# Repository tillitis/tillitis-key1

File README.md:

# Tillitis TKey

Read about current work in progress
[here](#current-work-in-progress-in-this-repository).

 *The TK1 PCB, also known as
TKey.*

## Introduction

The Tillitis TKey is an open source, open hardware FPGA-based USB
security token which can run generic applications while still
guaranteeing the security of its cryptographic assets.

The key behind guaranteeing key security even as a general computer is
the
[DICE-like](https://trustedcomputinggroup.org/work-groups/dice-architectures/)
measured boot or, when chaining apps, the combination of measured boot
and verified boot. You can read more about this in the introduction in
the [TKey Developer Handbook](https://dev.tillitis.se/castor/intro/).

[TKey Threat Model](doc/threat_model/threat_model.md).

With the right application, the TKey can be used for:

- authentication,
- cryptographic signing,
- encryption,
- root of trust,
- and more: it's a general computer!

If you want to know more about Tillitis and the TKey, visit:

- Main web: <https://tillitis.se/>
- Shop: <https://shop.tillitis.se/>
- Developer Handbook: <https://dev.tillitis.se/>
- Officially supported apps: <https://tillitis.se/download/>
- Other known apps: <https://dev.tillitis.se/projects/>

All of the TKey software, firmware, FPGA Verilog code, schematics and
PCB design files are open source, just like all trustworthy security
software and hardware should be.

## Licensing

Unless otherwise noted, the project sources are copyright Tillitis AB,
but you can redistribute it and/or modify it under the terms of the
BSD-2-Clause license.

Until Oct 29, 2025, the license was GPL-2.0 Only.

Each imported project is typically kept in its own directory with its
own LICENSE file.

### SPDX

The project uses single-line references to Unique License Identifiers
as defined by the Linux Foundation's [SPDX project](https://spdx.org/).
The line in each individual source file identifies the license
applicable to that file.

The current set of valid, predefined SPDX identifiers can be found on
the SPDX License List at:

https://spdx.org/licenses/

We attempt to follow the [REUSE
specification](https://reuse.software/).

### Notable imported projects

- ch552 firmware: `hw/usb_interface/ch552_fw/`

  Originally by WCH under MIT. Much changed by Tillitis.

- picorv32: `hw/application_fpga/core/picorv32`

  From https://github.com/YosysHQ/picorv32

  ISC.

- PicoRV32 custom ops: `hw/application_fpga/fw/tk1/picorv32/`

  CC-1.

- tkey-libs: `hw/application_fpga/tkey-libs/`

  BSD2. From https://github.com/tillitis/tkey-libs

## Repositories

This repository contains the FPGA design, the source of the
firmware/bootloader, and the source of the USB controller firmware.

Specific documentation regarding implementation is kept close to the
code/design in README files, typically in the same directory.

Note that development is ongoing. To avoid unexpected changes of
derived key material, please use a tagged release. Read the [Release
Notes](doc/release_notes.md) to keep up to date with changes and new
releases.

The TKey PCB [KiCad](https://www.kicad.org/) design files are kept in
a separate repository:

<https://github.com/tillitis/tk1-pcba>

The TP1 (TKey programmer 1) PCB design files and the firmware sources
are kept in:

<https://github.com/tillitis/tp1>

Note that the TP1 is only used for provisioning the FPGA bitstream
into flash or the FPGA configuration memory. It's not necessary if you
just want to develop apps for the TKey.

We use the tkey-libs libraries used for device app development in the
firmware, too:

https://github.com/tillitis/tkey-libs

but keep our own copy of it in the repo. See below.

## Building & flashing

These instructions assume you're using a Linux distribution. Most of
them also assume you're using our OCI image
[tkey-builder](https://ghcr.io/tillitis/tkey-builder). If you want to
run native tools, look in `contrib/Dockerfile` and
`contrib/buildtools.sh` for the tools and versions to use.

### FPGA

You need a [TKey
Unlocked](https://shop.tillitis.se/products/tkey-not-provisioned), a
[the TP1 TKey Programmer
board](https://shop.tillitis.se/products/tkey-dev-kit), and probably a
[Blinkinlabs CH55x Reset
Controller](https://shop-nl.blinkinlabs.com/products/ch55x-reset-controller)
to use this on real hardware.

Building is probably easiest using make and Podman.

To build everything and then flash the resulting bitstream with the
defaultapp in app slot 0 and the partition table copies in one go,
place the TKey Unlocked in the TP1, then do:

```
cd contrib
make flash
```

This uses the make target `prog_flash` in
`hw/application_fpga/Makefile` behind the scenes, but mounts your TP1
device into the container.

If you want to change the default app the TKey uses, change
`FLASH_APP_0` in the `hw/application_fpga/Makefile`.

To see all container targets:

```
cd contrib
make
```

See the [Tillitis Developer Handbook](https://dev.tillitis.se) for
more.

### USB Controller

The TKey uses a WCH CH552 chip as a USB controller. It has its own
firmware.

Build:

```
cd contrib
make run
cd hw/usb_interface/ch552_fw
make
```

To flash the controller with new firmware you need hardware like the
[Blinkinlabs CH55x Reset
Controller](https://shop-nl.blinkinlabs.com/products/ch55x-reset-controller)
and a USB-A to USB-C converter.

[Reset Controller source](https://github.com/Blinkinlabs/ch55x_programmer).

You also need [chprog](https://github.com/ole00/chprog).

The bootloader identifies itself as USB VID 4348, PID 55e0. To be able
to access it and run `chprog` without root you need to allow your user
to access it. Place `contrib/99-tillitis.rules` in `/etc/udev/rules.d`
and run `udevadm control --reload`. Now you can add your user to the
`dialout` group and access it.

1. Connect the Reset Controller to your computer through "DUT\_IN"/"PC".
2. Connect the TKey to "DUT\_OUT"/"DUT".
3. Press the "Bootloader" button.
4. Run `make flash_patched` in `hw/usb_interface/ch552_fw` outside of
   a container.

## Updating and working with tkey-libs

A copy of [tkey-libs](https://github.com/tillitis/tkey-libs) is kept
in `hw/application_fpga/tkey-libs`. This is mostly to avoid the
subtleties of Git submodules.

If you want to change something in tkey-libs, always change in the
upstream library at:

https://github.com/tillitis/tkey-libs

You can build with an out-of-tree copy if you set `LIBDIR`, for
example:

```
make LIBDIR=~/git/tkey-libs firmware.elf
```

When it's time to update the in-tree tkey-lib first tag the upstream
repo with an `fw` prefix, like `fw-1` even if it already has an
official version tag.

Easiest is probably to just remove the tkey-libs directory and then
git clone the desired tag. Use the entire repo, but remove the .-files
like `.git`, `.github`, et cetera. Something like:

```
$ rm -rf tkey-libs
$ git clone git@github.com:tillitis/tkey-libs.git
$ cd tkey-libs
$ git checkout fw-3
```

Note that you need to change the optimization flag in the tkey-libs'
Makefile to `-Os`.

# Current Work in Progress in this repository

We are updating the FPGA and firmware on TKey as part of the Castor
release. This update will simplify TKey’s usage, laying the groundwork
for future support of U2F/FIDO authentication.

You can track our progress in the
[Platform project](https://github.com/orgs/tillitis/projects/11/views/2).

Note that main branch is in development. We try to keep status of main
branch updated in the [release notes](/doc/release_notes.md#upcoming-release-castor).

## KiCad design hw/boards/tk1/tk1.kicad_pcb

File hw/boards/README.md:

# MTA1-USB PCB designs

## Boards

The KiCad board projects all follow this directory structure:

| Path | Description |
| ---  | --- |
| /project | KiCad 6 project |
| /project/gerbers | PCB release files |
| /project/test | Scripts / gateware used for production tests |

### mta1-usb-v1

This is the first production version of the MTA1-USB design.

Main features:
* Miniaturized hardware the size of a small USB stick.
* The Interface FPGA from the MTA1-USB-DEV design has been replaced with an Interface MCU running a USB-to-Serial converter firmware. This was done to ease development of the FPGA design.
* A touch sensor IC is provided instead of the switch for user presence detection.
* Test pads are provided on the bottom of the board for programming the SPI flash, and also for measuring extra GPIO pins. The 'MTA1-USB-V1-Programmer' board is designed to support this.

### mta1-usb-v1-programmer

This is a programming jig for the mta1-usb-v1 board.

### mta1-usb-dev

This is the original design, intended as a development platform. It is a larger PCB, that connects to a PC via a USB C cable. 

Main features:
* 2 ICE40 FPGAs.
* The first ICE40 (Interface FPGA) is connected to a USB C plug, and is loaded with a gateware that contains a soft USB device. This gateware acts as an USB-to-GPIO interface to the second ICE40.
* The second ICE40 (application FPGA) is loaded with a RISC-V soft core containing the security firmware. User applications are run on this gateware.
* The second ICE40 also has an input button for user presenence detection.
* An FTDI module is included for programming both the Application and Interface FPGAs.
* Both ICE40s can be configured to boot from included SPI flash memories, NVCM, or be live programmed from the FTDI module.
* All GPIO lines between the two FPGAs, as well as all programming signals, are exposed on 0.1" headers for probing.

## Libraries

### mta1-library

This is a shared KiCad library for all boards in the project.

### KiCad-RP Pico

This is a KiCad library for the Raspberry Pi Pico symbol and footprint. It was extracted from the [Kicad-RP-Pico](https://github.com/ncarandini/KiCad-RP-Pico) project. It is licensed under the [Creative Commons CC-BY-SA 4.0 License](https://creativecommons.org/licenses/by-sa/4.0/legalcode), with an exception exempting waving any control of derived works.

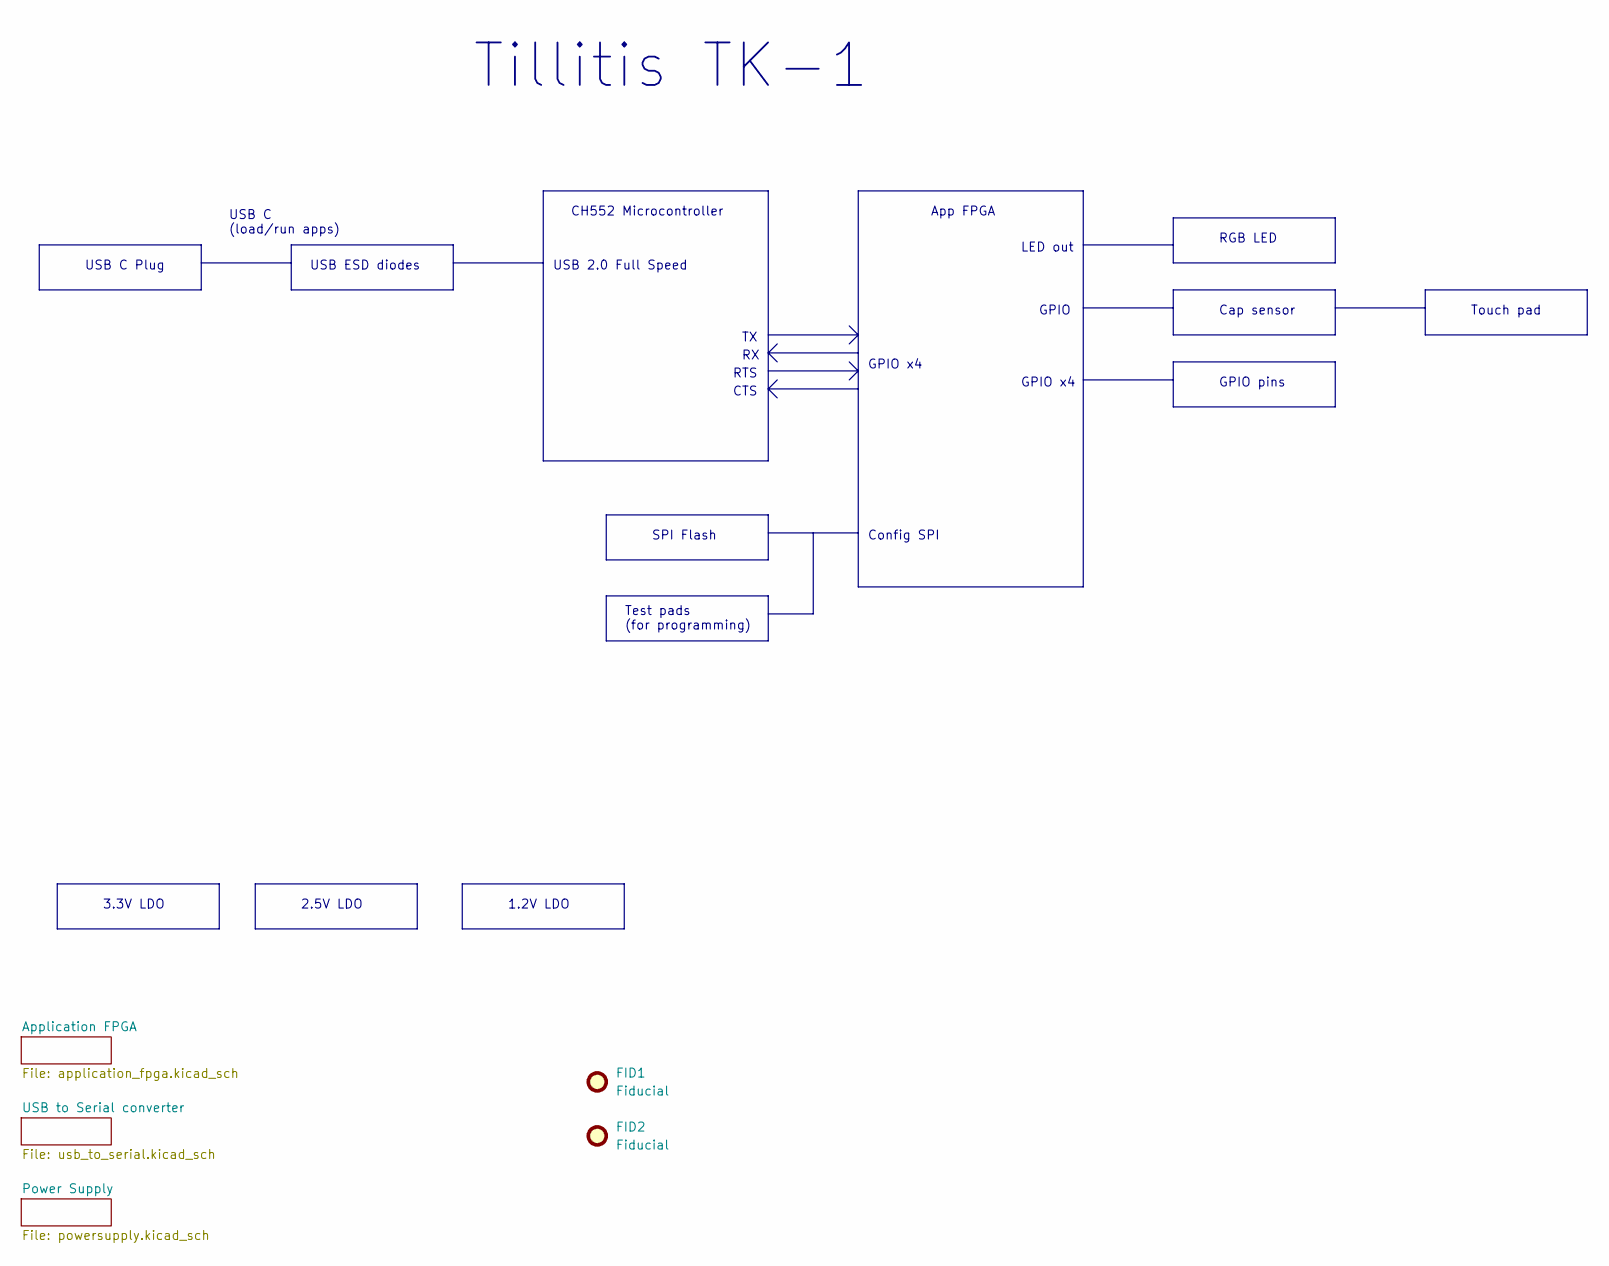
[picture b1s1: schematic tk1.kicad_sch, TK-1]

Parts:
FID1, FID2: Fiducial; Fiducial_0.75mm_Mask1.5mm

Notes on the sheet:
USB ESD diodes
Touch pad
GPIO x4
GPIO pins
Cap sensor
USB 2.0 Full Speed
RTS
USB C Plug
CH552 Microcontroller
RGB LED
USB C (load/run apps)
1.2V LDO
3.3V LDO
CTS
2.5V LDO
App FPGA
Config SPI
Tillitis TK-1
SPI Flash
GPIO
LED out
Test pads (for programming)

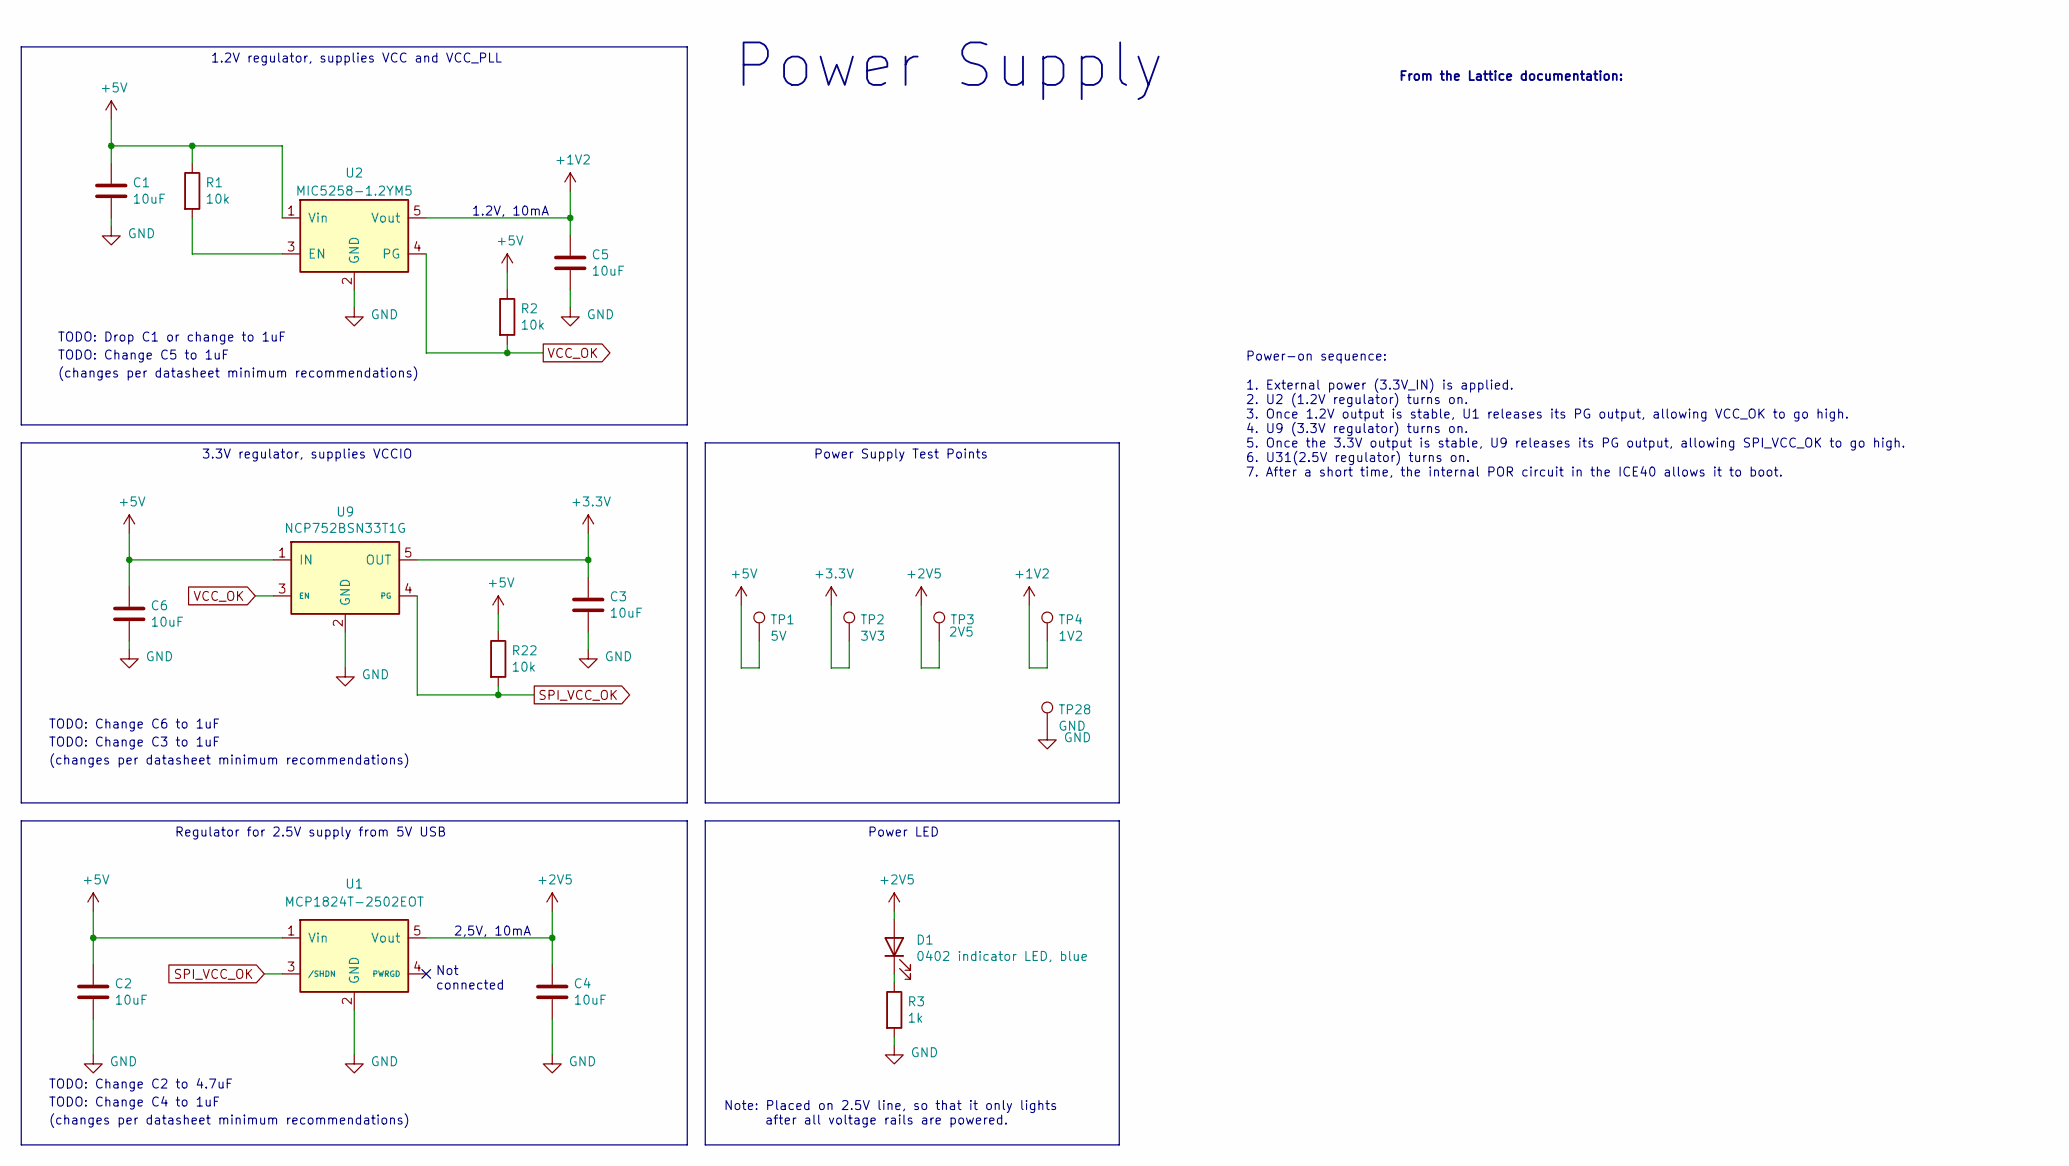
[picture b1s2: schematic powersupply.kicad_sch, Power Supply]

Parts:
C1, C2, C3, C4, C5, C6: 10uF; CAPC1608X09L
D1: 0402 indicator LED, blue; LED_0402_1005Metric; Manufacturer Part Number NCD0402B1
R1, R2, R22: 10k; ERJ2G(0402)_L
R3: 1k; ERJ2G(0402)_L
TP1: 5V; TestPoint_Pad_D1.0mm
TP2: 3V3; TestPoint_Pad_D1.0mm
TP3: 2V5; TestPoint_Pad_D1.0mm
TP4: 1V2; TestPoint_Pad_D1.0mm
TP28: GND; TestPoint_Pad_D1.0mm
U1: MCP1824T-2502EOT; SOT-23-5; Manufacturer Part Number MCP1824T-2502EOT
U2: MIC5258-1.2YM5; SOT-23-5; Manufacturer Part Number MIC5258-1.2YM5
U9: NCP752BSN33T1G; Manufacturer Part Number NCP752BSN33T1G

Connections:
+1V2: C5.1, TP4.1, U2.5 (Vout); also elsewhere on the board
+2V5: C4.1, D1.2 (A), TP3.1, U1.5 (Vout); also elsewhere on the board
+3V3: C3.1, TP2.1, U9.5 (OUT); also elsewhere on the board
+5V: C1.1, C2.1, C6.1, R1.1, R2.1, R22.1, TP1.1, U1.1 (Vin), U2.1 (Vin), U9.1 (IN); also elsewhere on the board
GND: C1.2, C2.2, C3.2, C4.2, C5.2, C6.2, R3.2, TP28.1, U1.2 (GND), U2.2 (GND), U9.2 (GND); also elsewhere on the board
unnamed: D1.1 (K), R3.1
unnamed: R1.2, U2.3 (EN)
SPI_VCC_OK: R22.2, U1.3 (/SHDN), U9.4 (PG)
VCC_OK: R2.2, U2.4 (PG), U9.3 (EN)

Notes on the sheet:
Power-on sequence: 1. External power (3.3V_IN) is applied. 2. U2 (1.2V regulator) turns on. 3. Once 1.2V output is stable, U1 releases its PG output, allowing VCC_OK to go high. 4. U9 (3.3V regulator) turns on. 5. Once the 3.3V output is stable, U9 releases its PG output, allowing SPI_VCC_OK to go 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
TODO: Change C2 to 4.7uF
(changes per datasheet minimum recommendations)
TODO: Change C6 to 1uF
2,5V, 10mA
Note: Placed on 2.5V line, so that it only lights after all voltage rails are powered.
TODO: Change C3 to 1uF
1.2V, 10mA
Power Supply
TODO: Drop C1 or change to 1uF
TODO: Change C5 to 1uF
From the Lattice documentation:
1.2V regulator, supplies VCC and VCC_PLL
3.3V regulator, supplies VCCIO
TODO: Change C4 to 1uF
Not connected
Power Supply Test Points
Power LED
Regulator for 2.5V supply from 5V USB

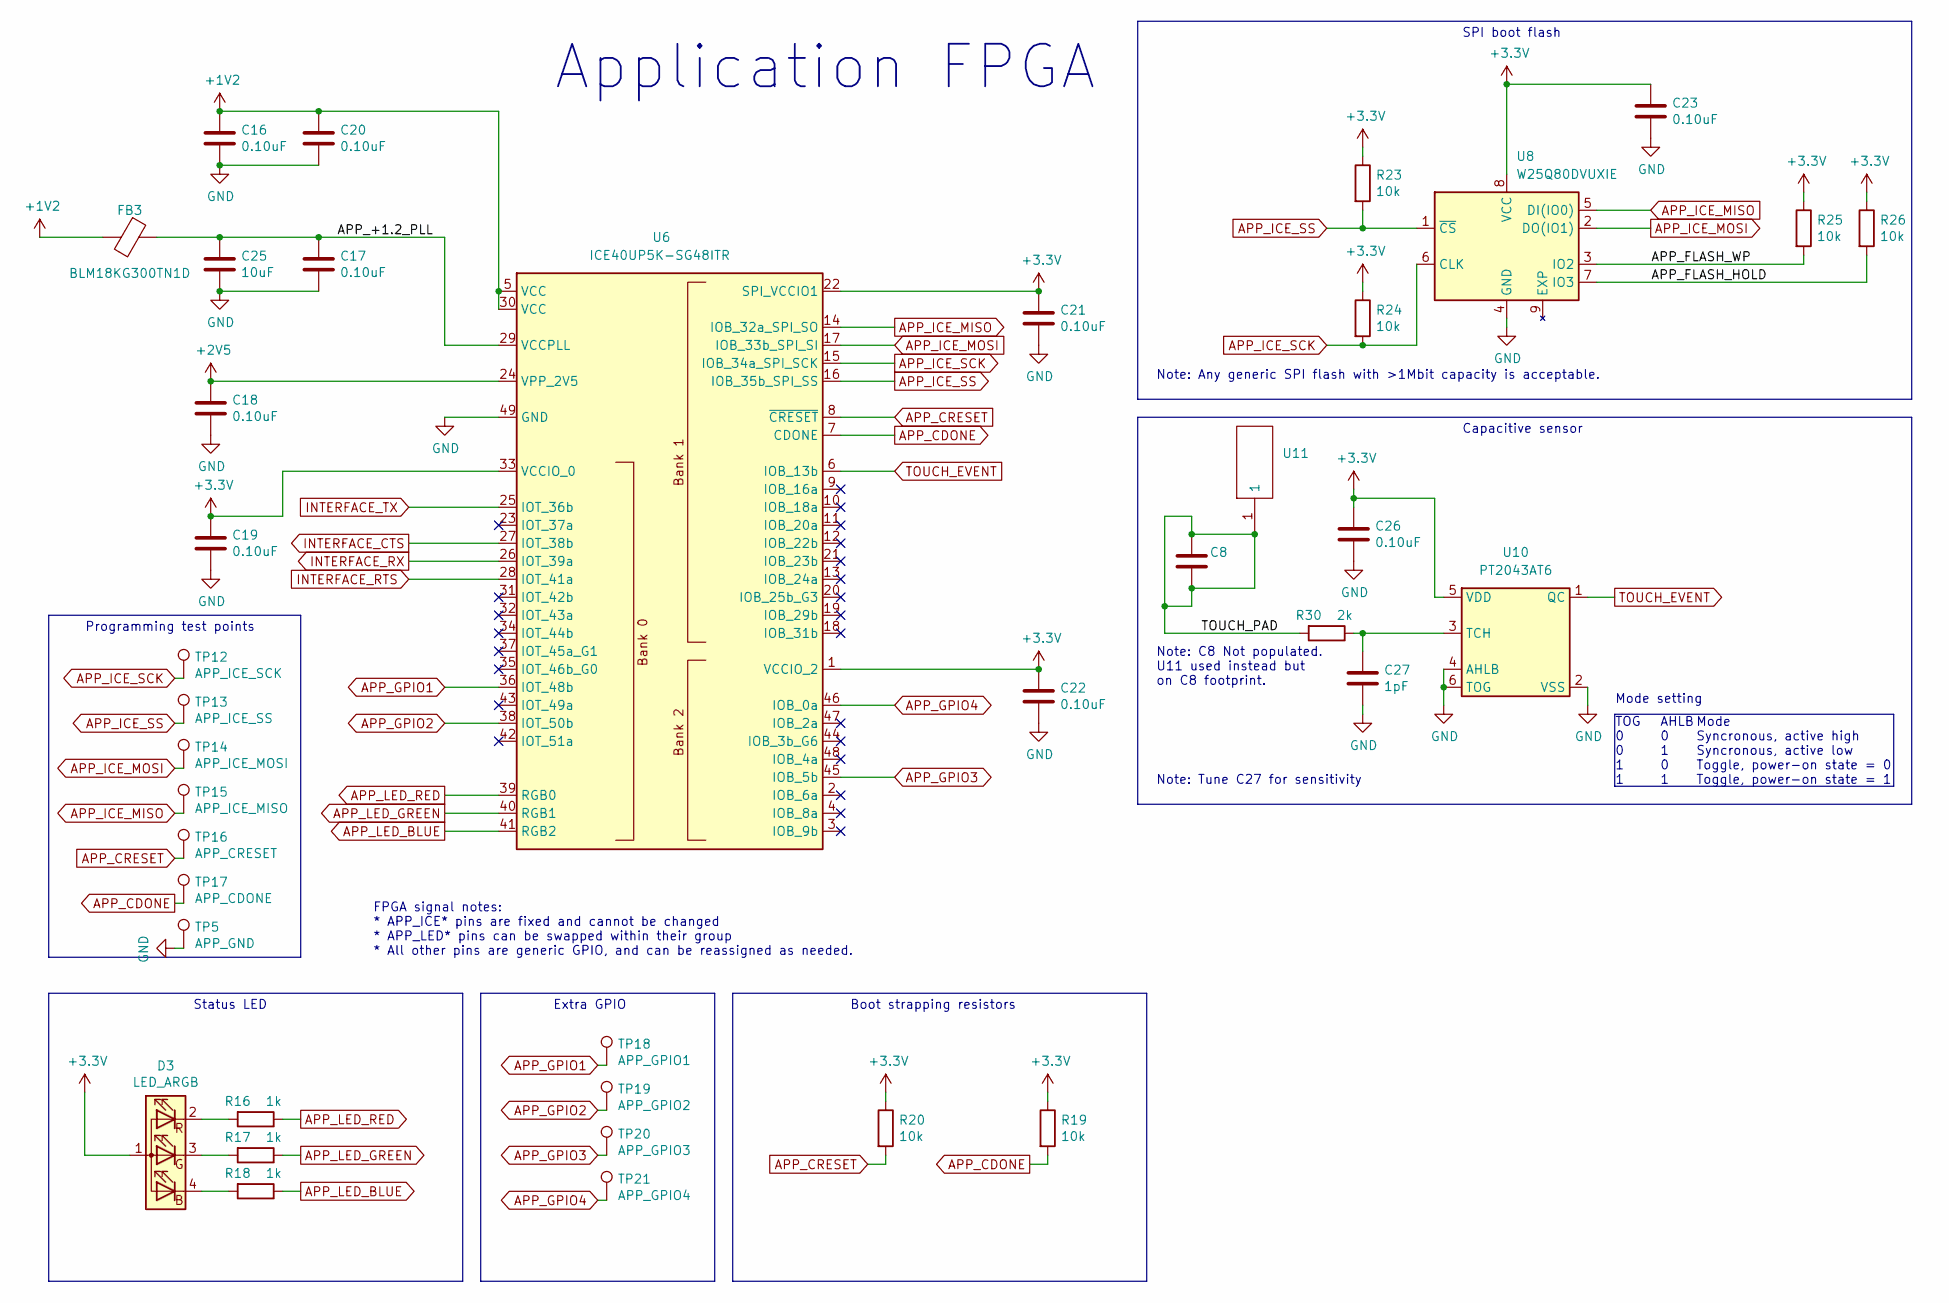
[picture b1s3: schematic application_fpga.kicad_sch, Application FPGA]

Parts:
C8: Manufacturer Part Number C3216X7R1H105K160AE
C16, C17, C18, C19, C20, C21, C22, C23, C26: 0.10uF; CAPC1005X06L
C25: 10uF; CAPC1608X09L
C27: 1pF; CAPC1005X06L
D3: LED_ARGB; 0402rgb-1010; Manufacturer Part Number FC-B1010RGBT-HG
FB3: BLM18KG300TN1D; Ferritbead_0603_1608Metric; Manufacturer Part Number BLM18KG300TN1D
R16, R17, R18: 1k; ERJ2G(0402)_L
R19, R20, R23, R24, R25, R26: 10k; ERJ2G(0402)_L
R30: 2k; ERJ2G(0402)_L
TP5: APP_GND; TestPoint_Pad_D1.0mm
TP12: APP_ICE_SCK; TestPoint_Pad_D1.0mm
TP13: APP_ICE_SS; TestPoint_Pad_D1.0mm
TP14: APP_ICE_MOSI; TestPoint_Pad_D1.0mm
TP15: APP_ICE_MISO; TestPoint_Pad_D1.0mm
TP16: APP_CRESET; TestPoint_Pad_D1.0mm
TP17: APP_CDONE; TestPoint_Pad_D1.0mm
TP18: APP_GPIO1; TestPoint_Pad_D1.0mm
TP19: APP_GPIO2; TestPoint_Pad_D1.0mm
TP20: APP_GPIO3; TestPoint_Pad_D1.0mm
TP21: APP_GPIO4; TestPoint_Pad_D1.0mm
U6: ICE40UP5K-SG48ITR; QFN-48-1EP_7x7mm_P0.5mm_EP5.6x5.6mm; Manufacturer Part Number ICE40UP5K-SG48ITR
U8: W25Q80DVUXIE; Manufacturer Part Number W25Q80DVUXIE
U10: PT2043AT6; SOT-23-6; Manufacturer Part Number PT2043AT6
U11: Mouser Part Number 571-1674954-1

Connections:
+1V2: C16.1, C20.1, FB3.2, U6.5 (VCC), U6.30 (VCC); also elsewhere on the board
+2V5: C18.1, U6.24 (VPP_2V5); also elsewhere on the board
+3V3: C19.1, C21.1, C22.1, C23.1, C26.1, D3.1 (A), R19.1, R20.1, R23.1, R24.1, R25.1, R26.1, U6.1 (VCCIO_2), U6.22 (SPI_VCCIO1), U6.33 (VCCIO_0), U8.8 (VCC), U10.5 (VDD); also elsewhere on the board
/Application FPGA/APP_+1.2_PLL: C17.1, C25.1, FB3.1, U6.29 (VCCPLL)
/Application FPGA/APP_FLASH_HOLD: R26.2, U8.7 (IO3)
/Application FPGA/APP_FLASH_WP: R25.2, U8.3 (IO2)
/Application FPGA/TOUCH_PAD: C8.1, C8.2, R30.2, U11.1
APP_CDONE: R19.2, TP17.1, U6.7 (CDONE)
APP_CRESET: R20.2, TP16.1, U6.8 (~CRESET)
APP_GPIO1: TP18.1, U6.36 (IOT_48b)
APP_GPIO2: TP19.1, U6.38 (IOT_50b)
APP_GPIO3: TP20.1, U6.45 (IOB_5b)
APP_GPIO4: TP21.1, U6.46 (IOB_0a)
APP_ICE_MISO: TP15.1, U6.14 (IOB_32a_SPI_SO), U8.5 (DI(IO0))
APP_ICE_MOSI: TP14.1, U6.17 (IOB_33b_SPI_SI), U8.2 (DO(IO1))
APP_ICE_SCK: R24.2, TP12.1, U6.15 (IOB_34a_SPI_SCK), U8.6 (CLK)
APP_ICE_SS: R23.2, TP13.1, U6.16 (IOB_35b_SPI_SS), U8.1 (~CS)
APP_LED_BLUE: R18.1, U6.41 (RGB2)
APP_LED_GREEN: R17.1, U6.40 (RGB1)
APP_LED_RED: R16.1, U6.39 (RGB0)
GND: C16.2, C17.2, C18.2, C19.2, C20.2, C21.2, C22.2, C23.2, C25.2, C26.2, C27.2, TP5.1, U6.49 (GND), U8.4 (GND), U10.2 (VSS), U10.4 (AHLB), U10.6 (TOG); also elsewhere on the board
INTERFACE_CTS: U6.27 (IOT_38b); also elsewhere on the board
INTERFACE_RTS: U6.28 (IOT_41a); also elsewhere on the board
INTERFACE_RX: U6.26 (IOT_39a); also elsewhere on the board
INTERFACE_TX: U6.25 (IOT_36b); also elsewhere on the board
unnamed: C27.1, R30.1, U10.3 (TCH)
unnamed: D3.2 (RK), R16.2
unnamed: D3.3 (GK), R17.2
unnamed: D3.4 (BK), R18.2
TOUCH_EVENT: U6.6 (IOB_13b), U10.1 (QC)

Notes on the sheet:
Application FPGA
Mode Syncronous, active high Syncronous, active low Toggle, power-on state = 0 Toggle, power-on state = 1
Capacitive sensor
SPI boot flash
FPGA signal notes: * APP_ICE* pins are fixed and cannot be changed * APP_LED* pins can be swapped within their group * All other pins are generic GPIO, and can be reassigned as needed.
Boot strapping resistors
AHLB 0 1 0 1
Status LED
Note: Tune C27 for sensitivity
Programming test points
Note: C8 Not populated. U11 used instead but on C8 footprint.
Mode setting
Note: Any generic SPI flash with >1Mbit capacity is acceptable.
Extra GPIO
TOG 0 0 1 1

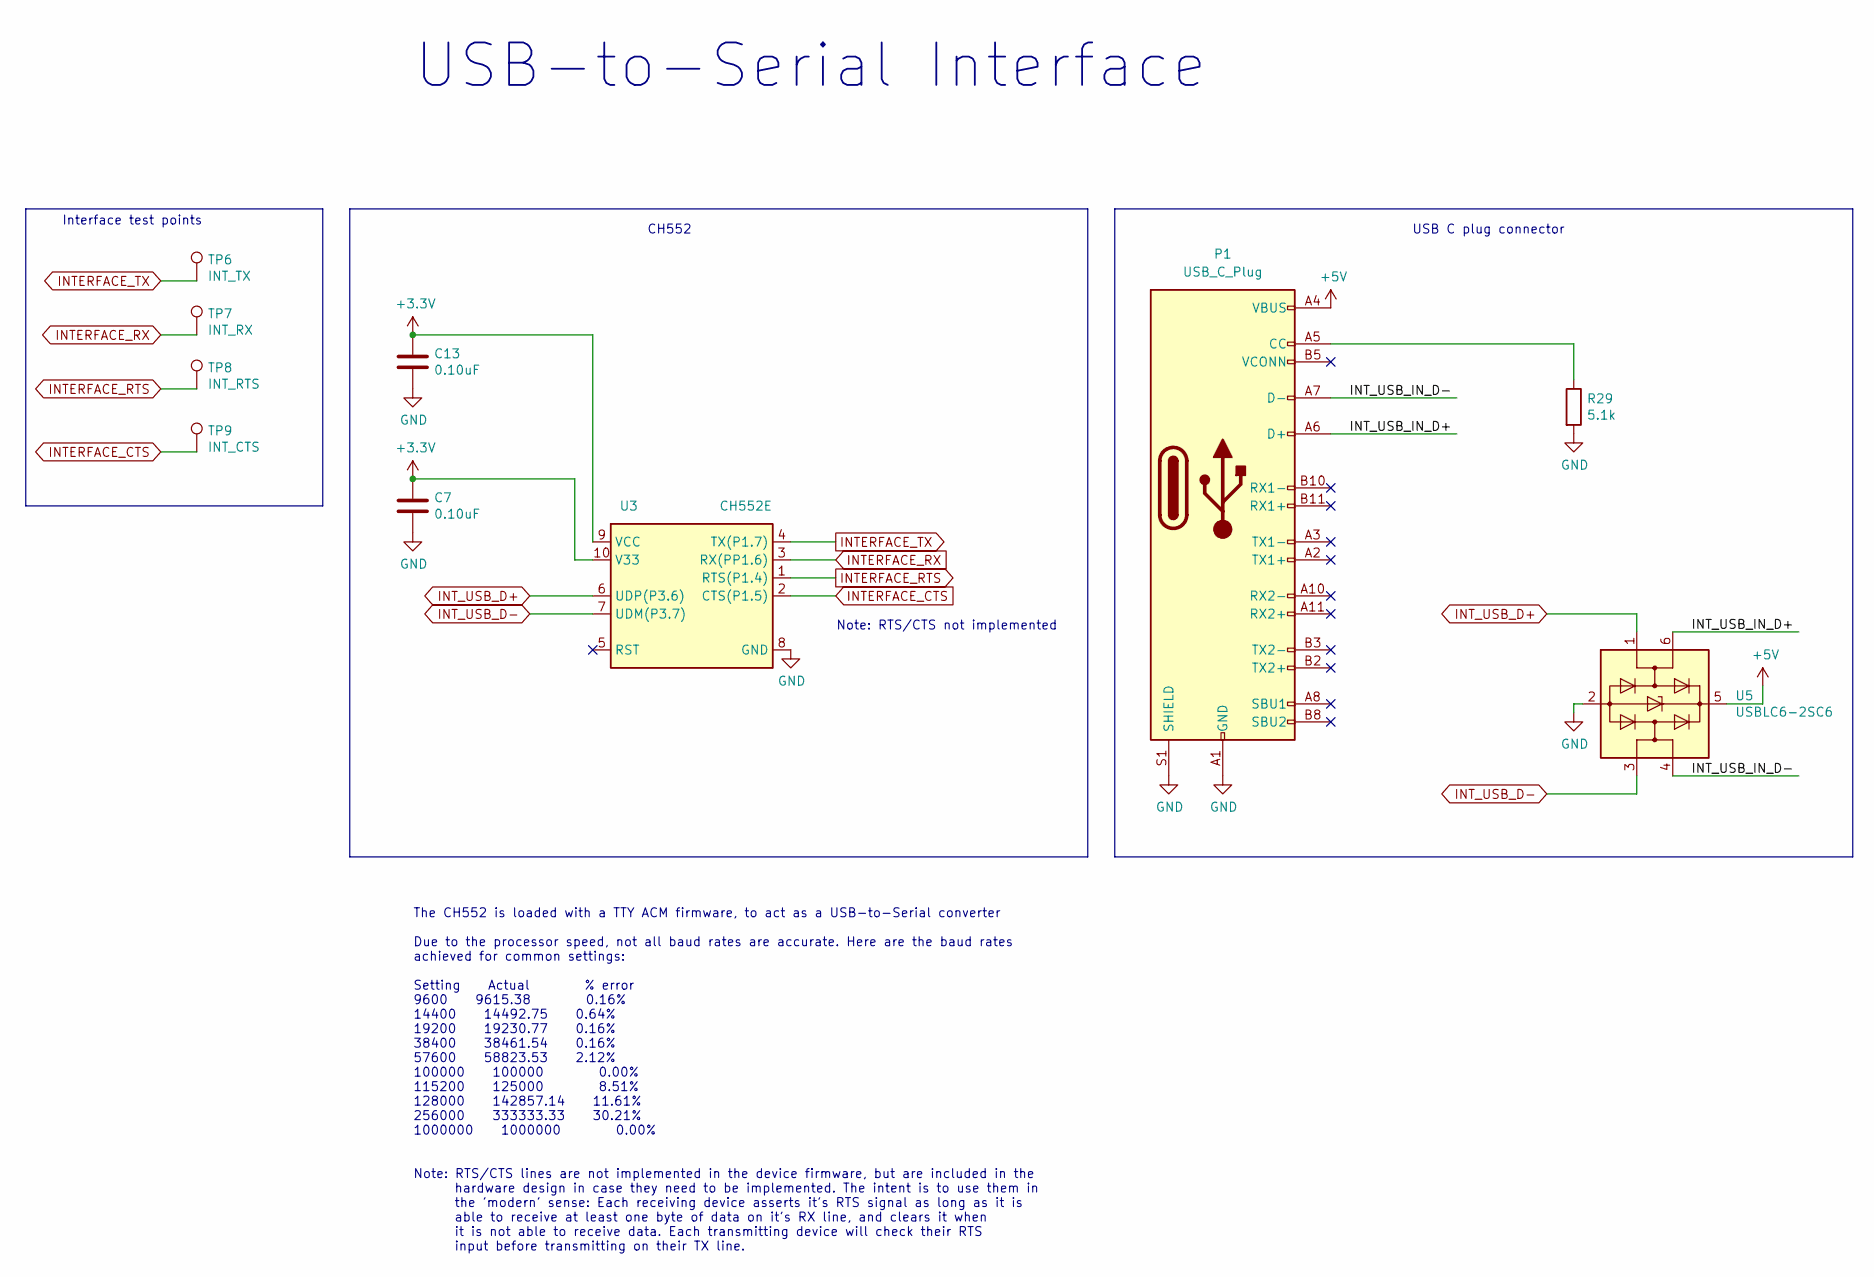
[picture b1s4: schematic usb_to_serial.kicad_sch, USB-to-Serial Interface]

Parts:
C7, C13: 0.10uF; CAPC1005X06L
P1: USB_C_Plug; U261-241N-4BS60; Manufacturer Part Number U261-241N-4BS60
R29: 5.1k; ERJ2G(0402)_L
TP6: INT_TX; TestPoint_Pad_D1.0mm
TP7: INT_RX; TestPoint_Pad_D1.0mm
TP8: INT_RTS; TestPoint_Pad_D1.0mm
TP9: INT_CTS; TestPoint_Pad_D1.0mm
U3: CH552E; MSOP-10_3x3mm_P0.5mm; Manufacturer Part Number CH552E
U5: USBLC6-2SC6; SOT-23-6; Manufacturer Part Number USBLC6-2SC6

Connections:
+3V3: C7.1, C13.1, U3.9 (VCC), U3.10 (V33); also elsewhere on the board
+5V: P1.A4 (VBUS), P1.A9 (VBUS), P1.B4 (VBUS), P1.B9 (VBUS), U5.5 (VBUS); also elsewhere on the board
/USB to Serial converter/INT_USB_IN_D+: P1.A6 (D+), U5.6 (I/O1)
/USB to Serial converter/INT_USB_IN_D-: P1.A7 (D-), U5.4 (I/O2)
GND: C7.2, C13.2, P1.A1 (GND), P1.A12 (GND), P1.B1 (GND), P1.B12 (GND), P1.S1 (SHIELD), R29.2, U3.8 (GND), U5.2 (GND); also elsewhere on the board
INTERFACE_CTS: TP9.1, U3.2 (CTS(P1.5)); also elsewhere on the board
INTERFACE_RTS: TP8.1, U3.1 (RTS(P1.4)); also elsewhere on the board
INTERFACE_RX: TP7.1, U3.3 (RX(PP1.6)); also elsewhere on the board
INTERFACE_TX: TP6.1, U3.4 (TX(P1.7)); also elsewhere on the board
INT_USB_D+: U3.6 (UDP(P3.6)), U5.1 (I/O1)
INT_USB_D-: U3.7 (UDM(P3.7)), U5.3 (I/O2)
unnamed: P1.A5 (CC), R29.1

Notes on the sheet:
USB C plug connector
CH552
USB-to-Serial Interface
The CH552 is loaded with a TTY ACM firmware, to act as a USB-to-Serial converter Due to the processor speed, not all baud rates are accurate. Here are the baud rates achieved for common settings: Setting Actual % error 9600 9615.38 0.16% 14400 14492.75 0.64% 19200 19230.77 0.16% 38400 38461.54 0.16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
Interface test points
Note: RTS/CTS not implemented

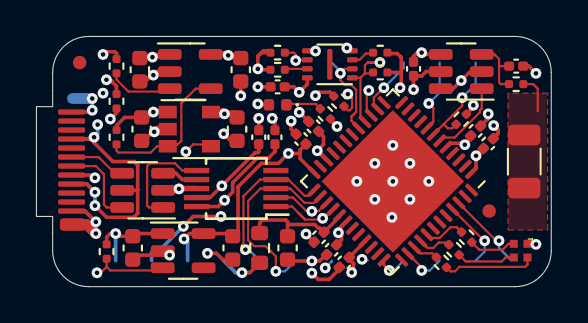
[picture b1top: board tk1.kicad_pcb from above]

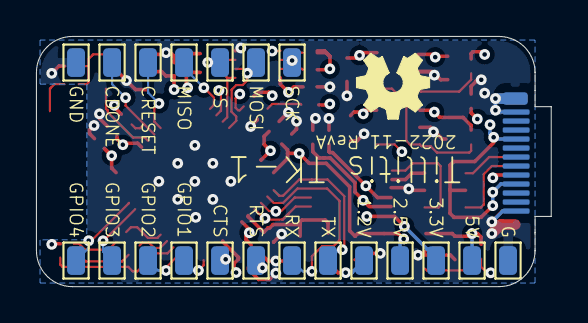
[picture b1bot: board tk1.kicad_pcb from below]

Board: 4 copper layers, 28.6 x 13.9 mm, 69 parts (20 on the bottom side), 40 nets.

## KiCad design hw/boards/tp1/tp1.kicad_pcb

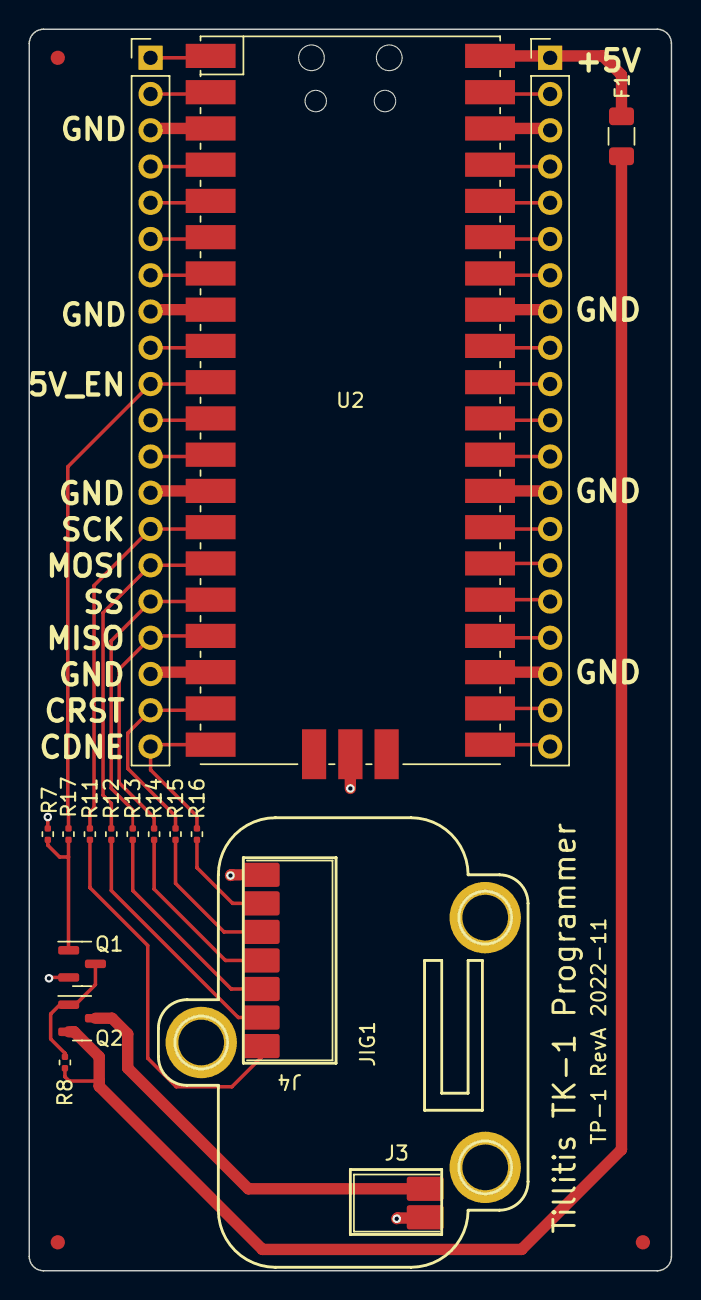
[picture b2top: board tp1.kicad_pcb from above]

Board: 2 copper layers, 45.0 x 87.0 mm, 21 parts (0 on the bottom side), 43 nets.

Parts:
F1: 50mA; Fuse_1206_3216Metric
FID1, FID2: Fiducial; Fiducial_1mm_Mask2mm
FIDe: Fiducial; Fiducial_1mm_Mask2mm
J1, J2: Conn_01x20; PinHeader_1x20_P2.54mm_Vertical
J3: BC-1-208
J4: BC-1-701
JIG1: mta1_usb_ch552_flat
Q1: AO3400A; SOT-23
Q2: AO3401A; SOT-23
R7, R8: 10K; ERJ2G(0402)_L
R11, R12, R13, R14, R15, R16, R17: 100R; ERJ2G(0402)_L
U2: Pico; RPi_Pico_SMD_reflow

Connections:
+5V: F1.1, J2.1, U2.40 (VBUS)
/5V_DUT: J3.1, Q2.3 (D)
/5V_EN: J1.10, R17.1, U2.10 (GPIO7)
/5V_FUSE: F1.2, Q2.2 (S), R8.2
/CDONE: J4.6, R16.1
/CDONE_U: J1.20, R16.2, U2.20 (GPIO15)
/CRESET: J4.5, R15.1
/CRESET_U: J1.19, R15.2, U2.19 (GPIO14)
/CTS_U: J2.19, U2.22 (GPIO17)
/GPIO1_U: J2.17, U2.24 (GPIO18)
/GPIO2_U: J2.16, U2.25 (GPIO19)
/GPIO3_U: J2.15, U2.26 (GPIO20)
/GPIO4_U: J2.14, U2.27 (GPIO21)
/MISO: J4.4, R14.1
/MISO_U: J1.17, R14.2, U2.17 (GPIO13)
/MOSI: J4.2, R12.1
/MOSI_U: J1.15, R12.2, U2.15 (GPIO11)
/PICO22: J2.12, U2.29 (GPIO22)
/PICO26: J2.10, U2.31 (GPIO26_ADC0)
/PICO27: J2.9, U2.32 (GPIO27_ADC1)
/PICO28: J2.7, U2.34 (GPIO28_ADC2)
/PICO_0: J1.1, U2.1 (GPIO0)
/PICO_1: J1.2, U2.2 (GPIO1)
/PICO_2: J1.4, U2.4 (GPIO2)
/PICO_3: J1.5, U2.5 (GPIO3)
/PICO_3V3: J2.5, U2.36 (3V3)
/PICO_3V3_EN: J2.4, U2.37 (3V3_EN)
/PICO_4: J1.6, U2.6 (GPIO4)
/PICO_5: J1.7, U2.7 (GPIO5)
/PICO_6: J1.9, U2.9 (GPIO6)
/PICO_ADC_VREF: J2.6, U2.35 (ADC_VREF)
/PICO_RUN: J2.11, U2.30 (RUN)
/PICO_VSYS: J2.2, U2.39 (VSYS)
/RTS_U: J2.20, U2.21 (GPIO16)
/RX_U: J1.12, U2.12 (GPIO9)
/SCK: J4.1, R11.1
/SCK_U: J1.14, R11.2, U2.14 (GPIO10)
/SS: J4.3, R13.1
/SS_U: J1.16, R13.2, U2.16 (GPIO12)
/TX_U: J1.11, U2.11 (GPIO8)
GND: J1.3, J1.8, J1.13, J1.18, J2.3, J2.8, J2.13, J2.18, J3.2, J4.7, Q1.2 (S), R7.1, U2.3 (GND), U2.8 (GND), U2.13 (GND), U2.18 (GND), U2.23 (GND), U2.28 (GND), U2.33 (AGND), U2.38 (GND), U2.42 (GND)
unnamed: Q1.1 (G), R7.2, R17.2
unnamed: Q1.3 (D), Q2.1 (G), R8.1

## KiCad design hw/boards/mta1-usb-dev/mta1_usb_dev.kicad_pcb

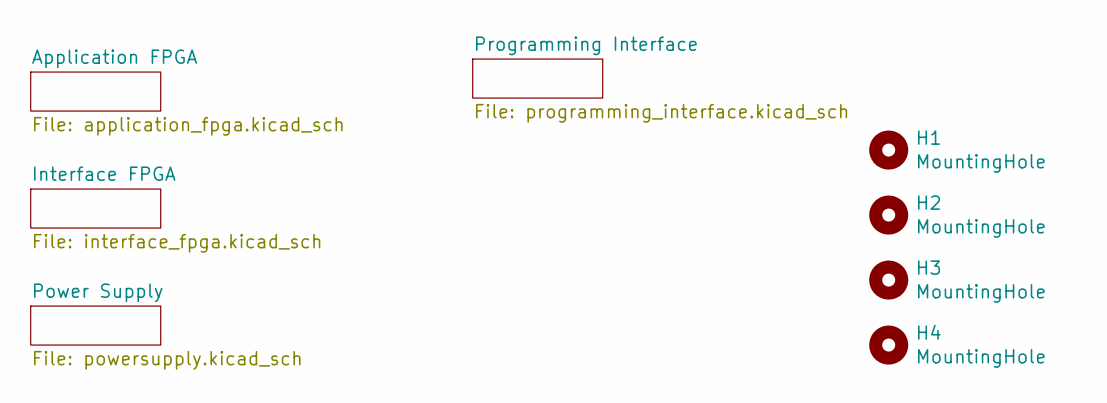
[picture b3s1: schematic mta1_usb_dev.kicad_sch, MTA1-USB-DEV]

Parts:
H1, H2, H3, H4: MountingHole; MountingHole_3.2mm_M3_DIN965_Pad_TopBottom

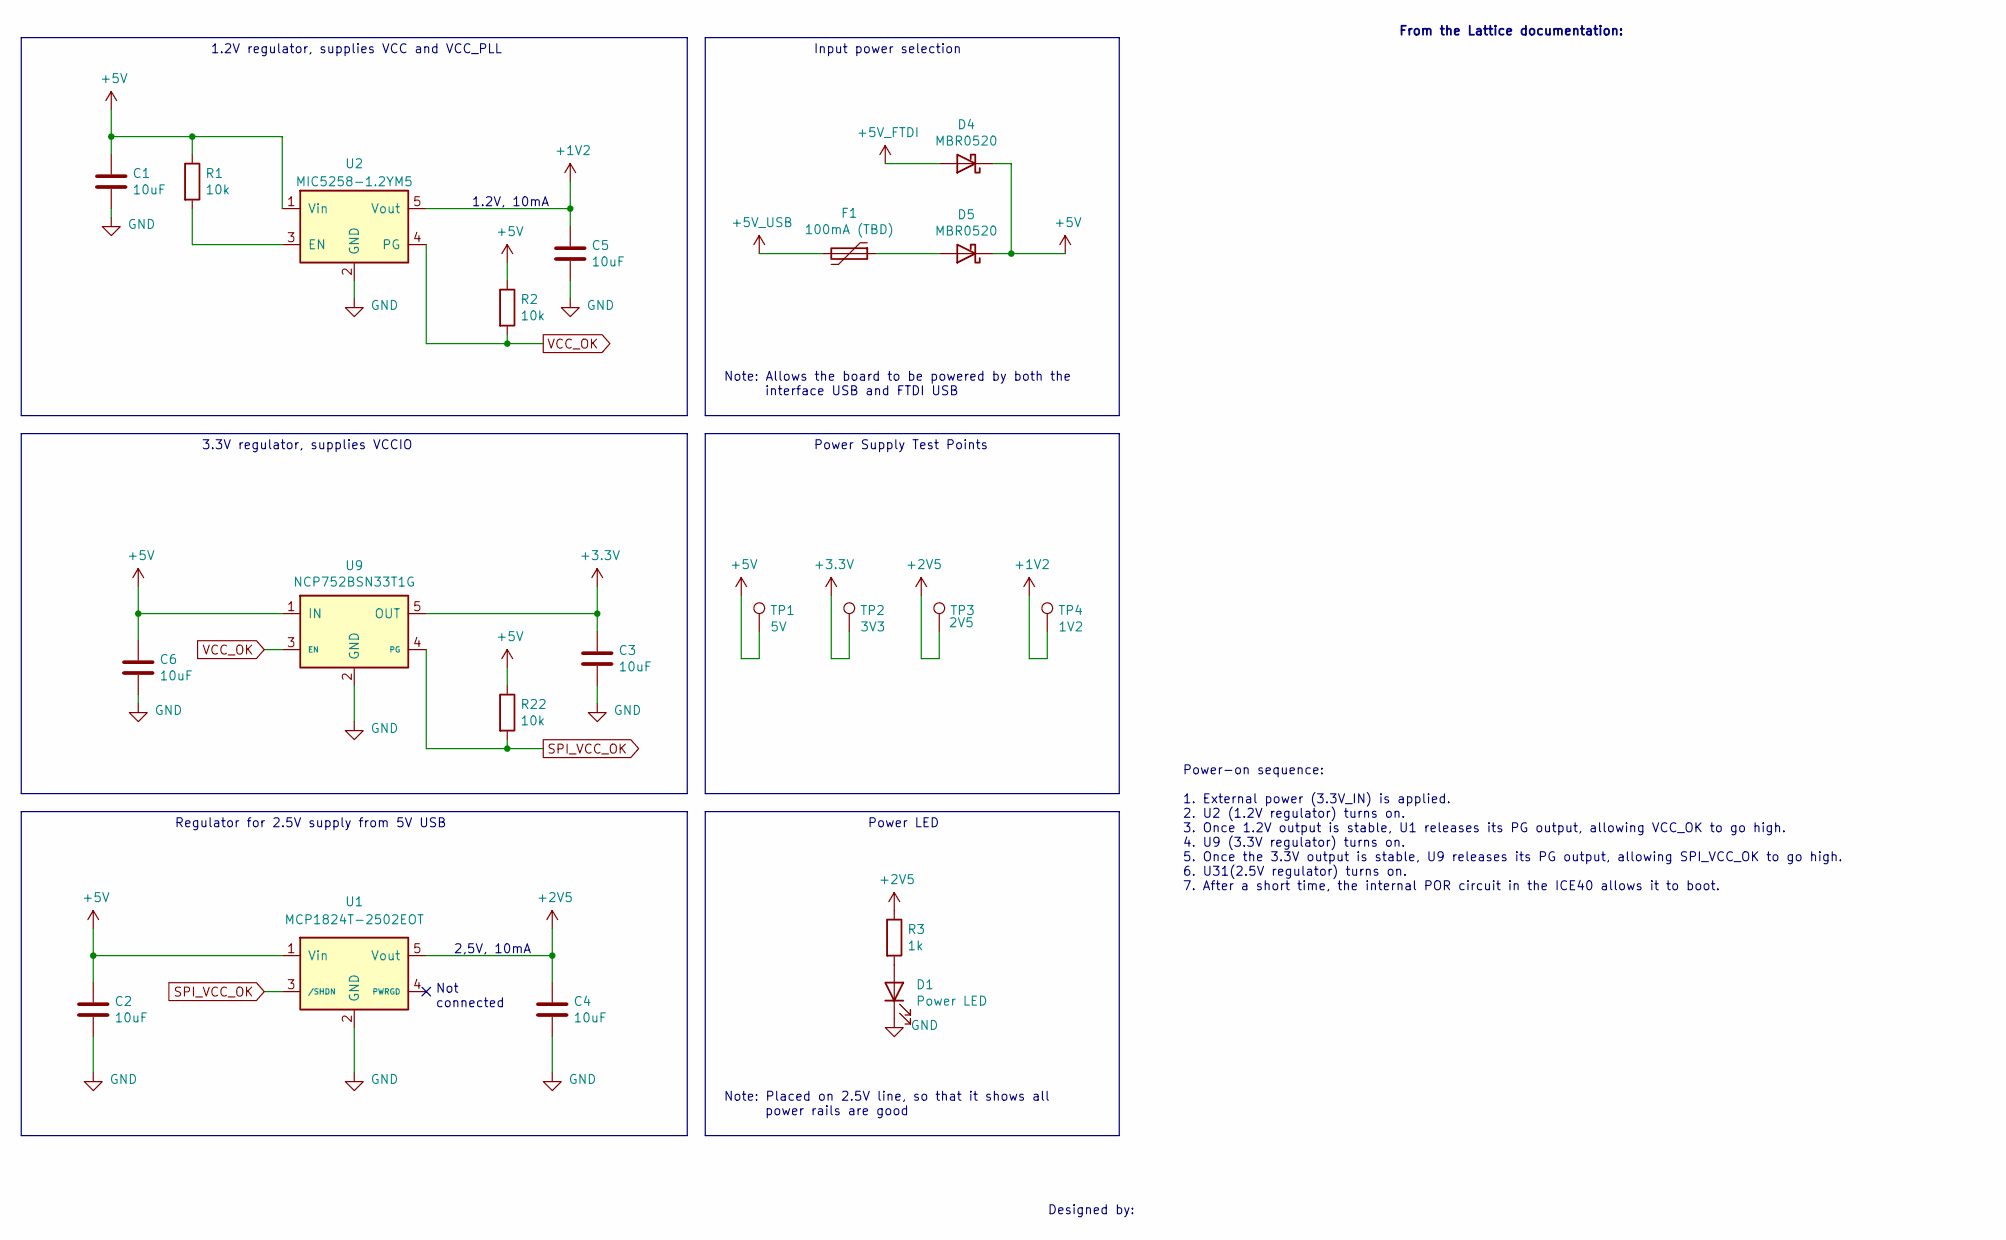
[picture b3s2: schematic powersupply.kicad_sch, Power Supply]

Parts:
C1, C2, C3, C4, C5, C6: 10uF; CAPC1608X09L
D1: Power LED; LED_0402_1005Metric
D4, D5: MBR0520; D_SOD-123
F1: 100mA (TBD); Fuse_1206_3216Metric
R1, R2, R22: 10k; ERJ2G(0402)_L
R3: 1k; ERJ2G(0402)_L
TP1: 5V; TestPoint_Pad_D1.0mm
TP2: 3V3; TestPoint_Pad_D1.0mm
TP3: 2V5; TestPoint_Pad_D1.0mm
TP4: 1V2; TestPoint_Pad_D1.0mm
U1: MCP1824T-2502EOT; SOT-23-5
U2: MIC5258-1.2YM5; SOT-23-5
U9: NCP752BSN33T1G

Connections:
+1V2: C5.1, TP4.1, U2.5 (Vout); also elsewhere on the board
+2V5: C4.1, R3.1, TP3.1, U1.5 (Vout); also elsewhere on the board
+3V3: C3.1, TP2.1, U9.5 (OUT); also elsewhere on the board
+5V: C1.1, C2.1, C6.1, D4.1 (K), D5.1 (K), R1.1, R2.1, R22.1, TP1.1, U1.1 (Vin), U2.1 (Vin), U9.1 (IN)
+5V_FTDI: D4.2 (A); also elsewhere on the board
+5V_USB: F1.2; also elsewhere on the board
GND: C1.2, C2.2, C3.2, C4.2, C5.2, C6.2, D1.1 (K), U1.2 (GND), U2.2 (GND), U9.2 (GND); also elsewhere on the board
unnamed: D1.2 (A), R3.2
unnamed: D5.2 (A), F1.1
unnamed: R1.2, U2.3 (EN)
SPI_VCC_OK: R22.2, U1.3 (/SHDN), U9.4 (PG)
VCC_OK: R2.2, U2.4 (PG), U9.3 (EN)

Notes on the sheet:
Power-on sequence: 1. External power (3.3V_IN) is applied. 2. U2 (1.2V regulator) turns on. 3. Once 1.2V output is stable, U1 releases its PG output, allowing VCC_OK to go high. 4. U9 (3.3V regulator) turns on. 5. Once the 3.3V output is stable, U9 releases its PG output, allowing SPI_VCC_OK to go 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
Note: Allows the board to be powered by both the interface USB and FTDI USB
2,5V, 10mA
Note: Placed on 2.5V line, so that it shows all power rails are good
Designed by:
Input power selection
1.2V, 10mA
From the Lattice documentation:
1.2V regulator, supplies VCC and VCC_PLL
3.3V regulator, supplies VCCIO
Not connected
Power Supply Test Points
Power LED
Regulator for 2.5V supply from 5V USB
